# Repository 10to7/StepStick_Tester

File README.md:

StepStick_Tester
================

**Warning** _currently untested, may contain errors._

A tester for stepsticks/Pololu drivers
and connects to the AS5055A module.

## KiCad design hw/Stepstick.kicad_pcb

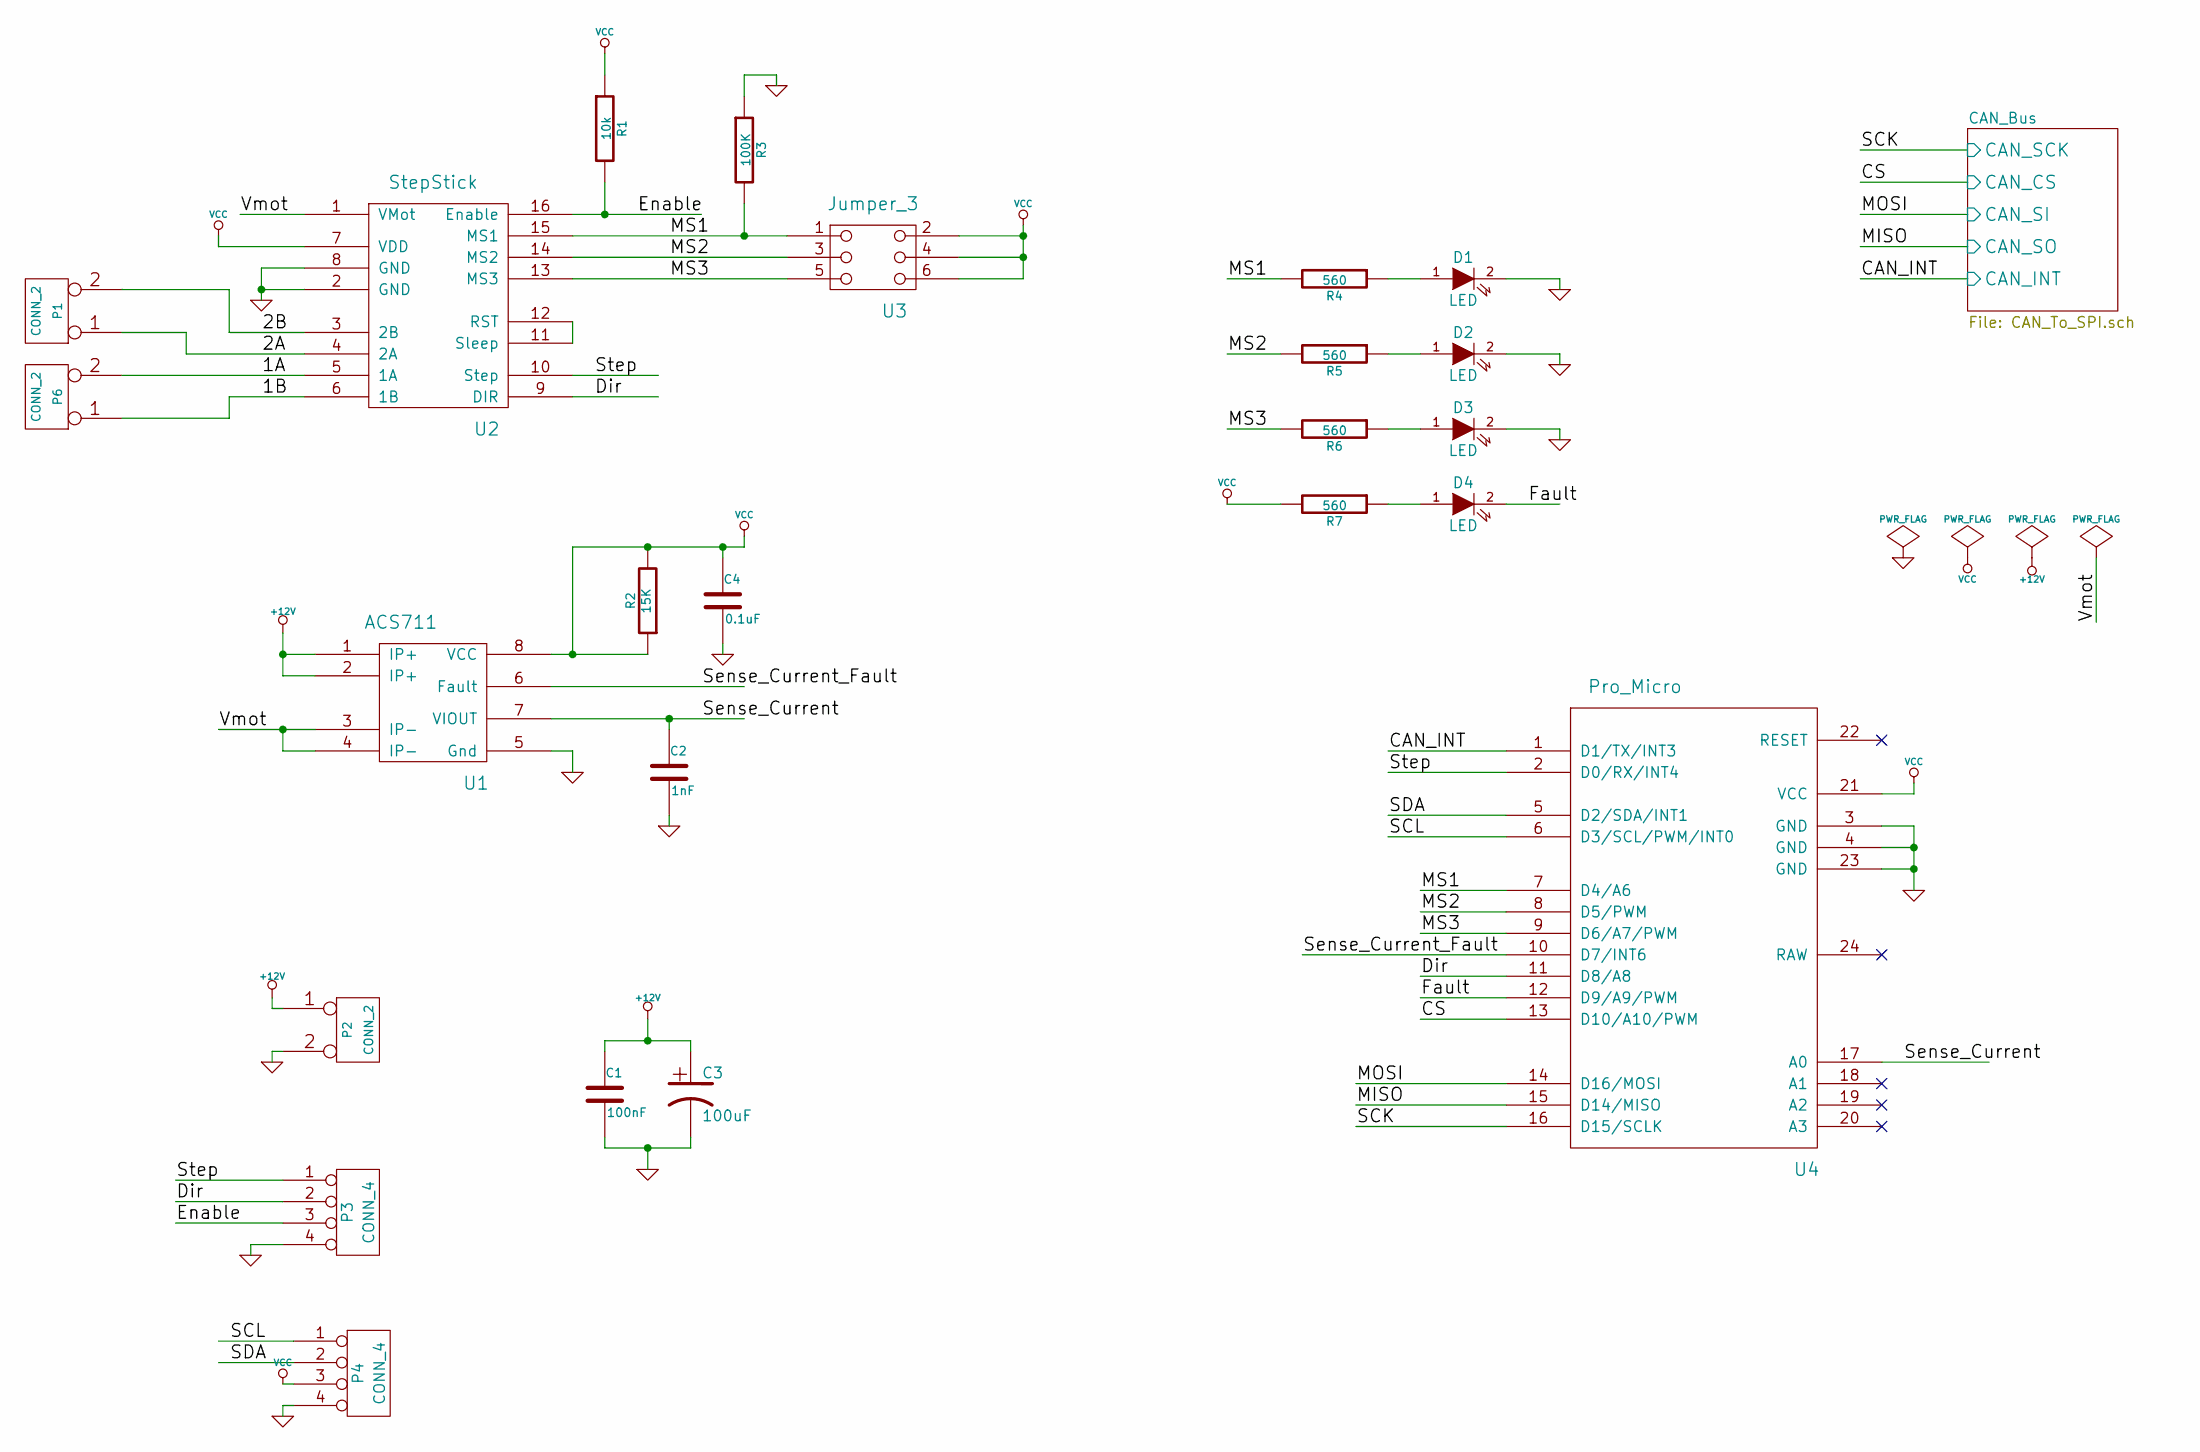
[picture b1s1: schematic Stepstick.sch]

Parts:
C1: 100nF
C2: 1nF
C3: 100uF
C4: 0.1uF
D1, D2, D3, D4: LED
P1, P2, P6: CONN_2
P3, P4: CONN_4
R1: 10k
R2: 15K
R3: 100K
R4, R5, R6, R7: 560
U1: ACS711
U2: StepStick
U3: Jumper_3
U4: Pro_Micro

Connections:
+12V: C1.1, C3.1, P2.1, U1.1 (IP+), U1.2 (IP+)
/1A: P6.2 (PM), U2.5 (1A)
/1B: P6.1, U2.6 (1B)
/2A: P1.1, U2.4 (2A)
/2B: P1.2 (PM), U2.3 (2B)
/CAN_Bus/CAN_CS: U4.13 (D10/A10/PWM); also elsewhere on the board
/CAN_Bus/CAN_INT: U4.1 (D1/TX/INT3); also elsewhere on the board
/CAN_Bus/CAN_SCK: U4.16 (D15/SCLK); also elsewhere on the board
/CAN_Bus/CAN_SI: U4.14 (D16/MOSI); also elsewhere on the board
/CAN_Bus/CAN_SO: U4.15 (D14/MISO); also elsewhere on the board
/Dir: P3.2, U2.9 (DIR), U4.11 (D8/A8)
/Enable: P3.3, R1.2, U2.16 (Enable)
/Fault: D4.2 (K), U4.12 (D9/A9/PWM)
/MS1: R3.2, R4.2, U2.15 (MS1), U3.1, U4.7 (D4/A6)
/MS2: R5.2, U2.14 (MS2), U3.3, U4.8 (D5/PWM)
/MS3: R6.2, U2.13 (MS3), U3.5, U4.9 (D6/A7/PWM)
/SCL: P4.1, U4.6 (D3/SCL/PWM/INT0)
/SDA: P4.2, U4.5 (D2/SDA/INT1)
/Sense_Current: C2.1, U1.7 (VIOUT), U4.17 (A0)
/Sense_Current_Fault: U1.6 (Fault), U4.10 (D7/INT6)
/Step: P3.1, U2.10 (Step), U4.2 (D0/RX/INT4)
/Vmot: U1.3 (IP-), U1.4 (IP-), U2.1 (VMot)
GND: C1.2, C2.2, C3.2, C4.2, D1.2 (K), D2.2 (K), D3.2 (K), P2.2 (PM), P3.4, P4.4, R3.1, U1.5 (Gnd), U2.2 (GND), U2.8 (GND), U4.3 (GND), U4.4 (GND), U4.23 (GND); also elsewhere on the board
unnamed: D1.1 (A), R4.1
unnamed: D2.1 (A), R5.1
unnamed: D3.1 (A), R6.1
unnamed: D4.1 (A), R7.1
unnamed: U2.11 (Sleep), U2.12 (RST)
VCC: C4.1, P4.3, R1.1, R2.1, R2.2, R7.2, U1.8 (VCC), U2.7 (VDD), U3.2, U3.4, U3.6, U4.21 (VCC); also elsewhere on the board

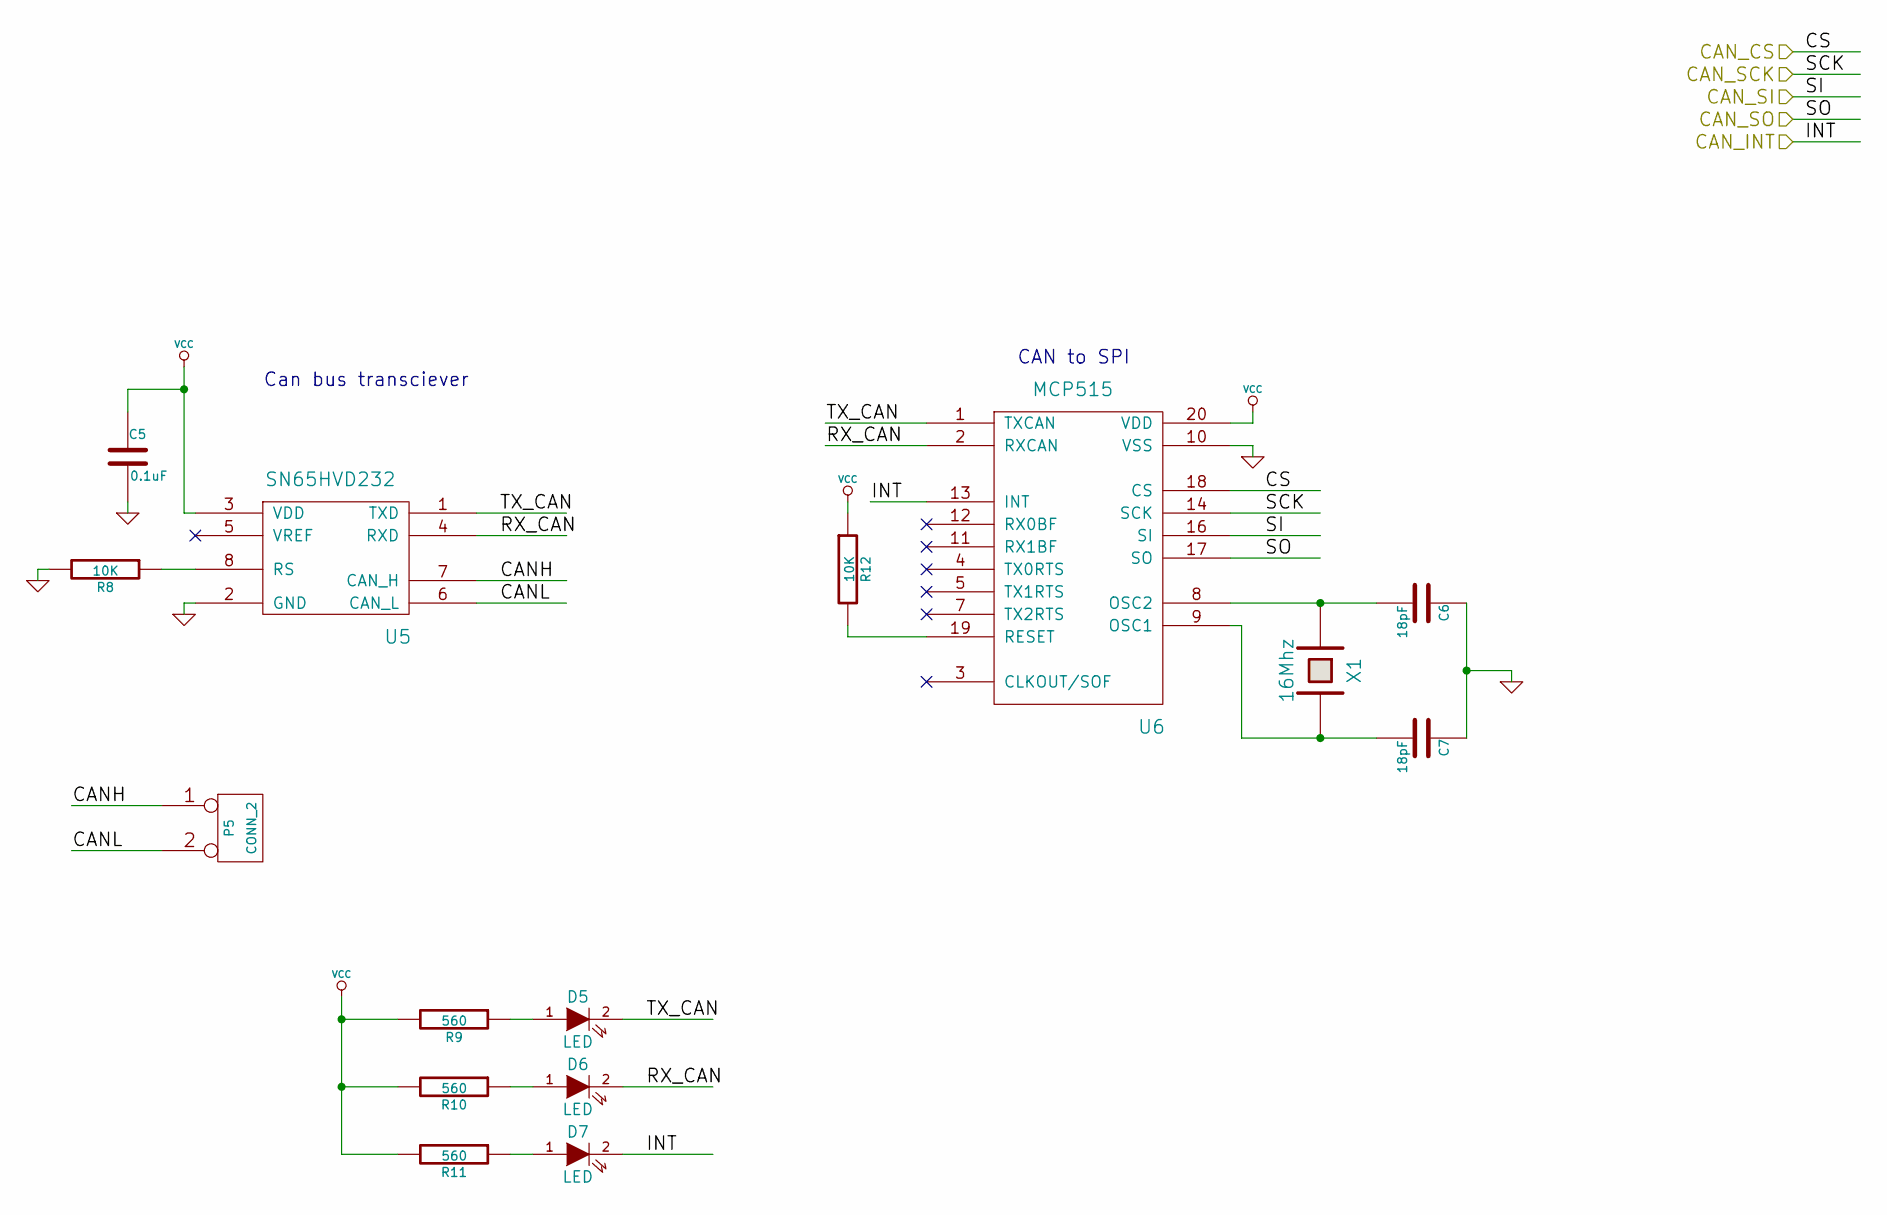
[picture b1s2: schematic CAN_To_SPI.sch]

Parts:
C5: 0.1uF
C6, C7: 18pF
D5, D6, D7: LED
P5: CONN_2
R8, R12: 10K
R9, R10, R11: 560
U5: SN65HVD232
U6: MCP515
X1: 16Mhz

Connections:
/CAN_Bus/CANH: P5.1, U5.7 (CAN_H)
/CAN_Bus/CANL: P5.2 (PM), U5.6 (CAN_L)
/CAN_Bus/CAN_CS: U6.18 (CS); also elsewhere on the board
/CAN_Bus/CAN_INT: D7.2 (K), U6.13 (INT); also elsewhere on the board
/CAN_Bus/CAN_SCK: U6.14 (SCK); also elsewhere on the board
/CAN_Bus/CAN_SI: U6.16 (SI); also elsewhere on the board
/CAN_Bus/CAN_SO: U6.17 (SO); also elsewhere on the board
/CAN_Bus/RX_CAN: D6.2 (K), U5.4 (RXD), U6.2 (RXCAN)
/CAN_Bus/TX_CAN: D5.2 (K), U5.1 (TXD), U6.1 (TXCAN)
GND: C5.2, C6.1, C7.1, R8.2, U5.2 (GND), U6.10 (VSS); also elsewhere on the board
unnamed: C6.2, U6.8 (OSC2), X1.1
unnamed: C7.2, U6.9 (OSC1), X1.2
unnamed: D5.1 (A), R9.1
unnamed: D6.1 (A), R10.1
unnamed: D7.1 (A), R11.1
unnamed: R8.1, U5.8 (RS)
unnamed: R12.2, U6.19 (RESET)
VCC: C5.1, R9.2, R10.2, R11.2, R12.1, U5.3 (VDD), U6.20 (VDD); also elsewhere on the board

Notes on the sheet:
Can bus transciever
CAN to SPI

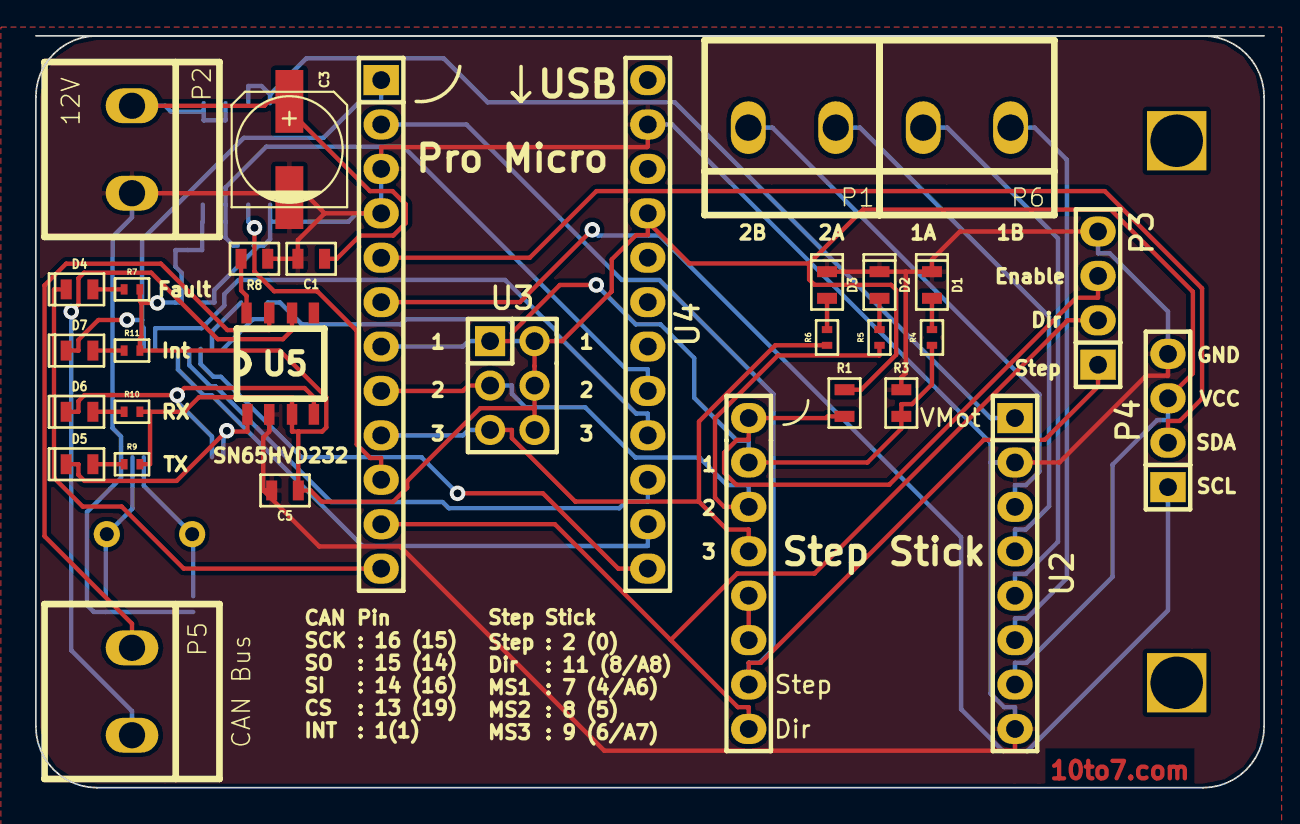
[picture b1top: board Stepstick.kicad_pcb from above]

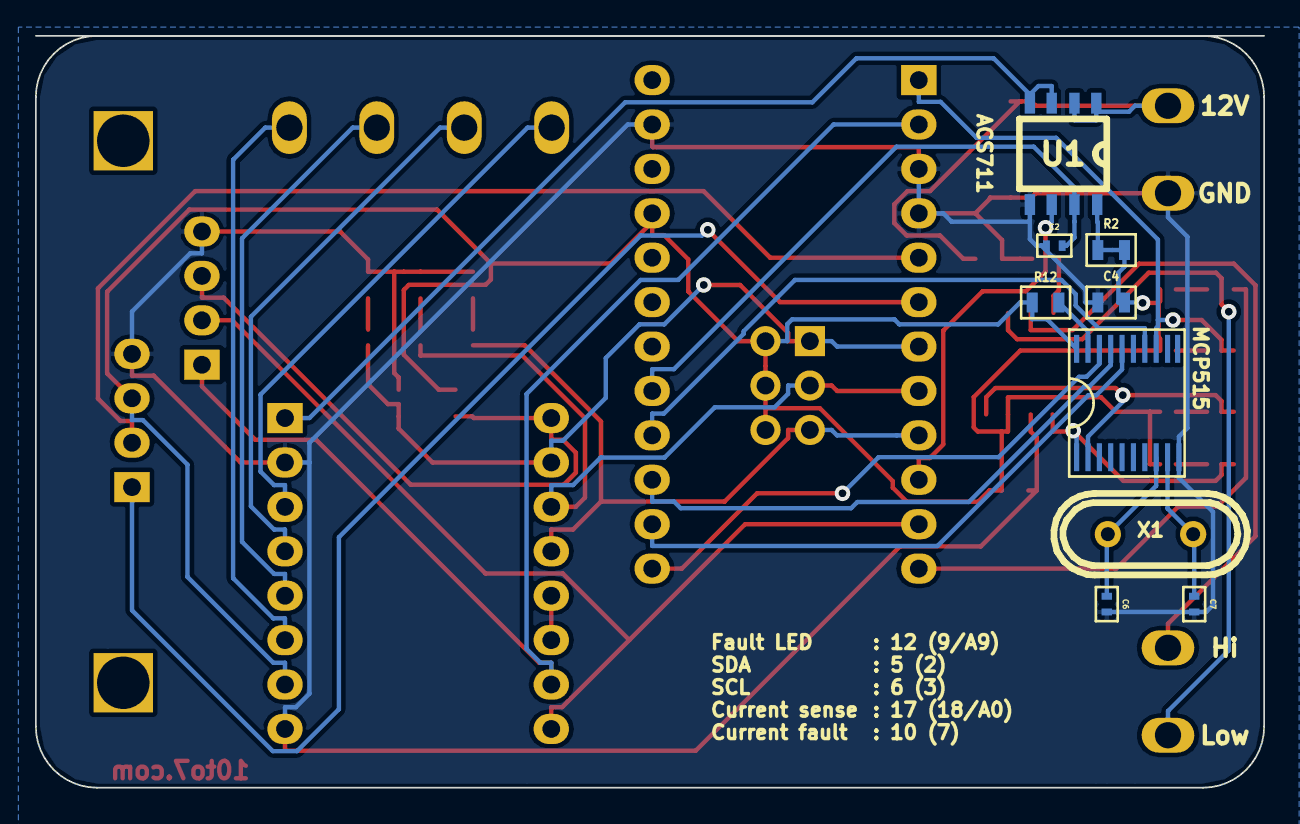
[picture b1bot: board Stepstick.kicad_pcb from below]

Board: 2 copper layers, 70.2 x 43.0 mm, 41 parts (9 on the bottom side), 40 nets.

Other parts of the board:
3mmHole, 3mmHole_2: VAL**; 3mmHole

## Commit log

2014-06-06 Added Schematic
2014-06-09 Added some of the netlist
2014-06-12 pcb layout completed
2014-07-06 corrected the CAN transceiver in the schematic - 3V3 version was selected incorrectly.
